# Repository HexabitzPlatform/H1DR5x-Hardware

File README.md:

# H1DR5x-Hardware
Hexabitz 10Base-T Ethernet Module Hardware Design

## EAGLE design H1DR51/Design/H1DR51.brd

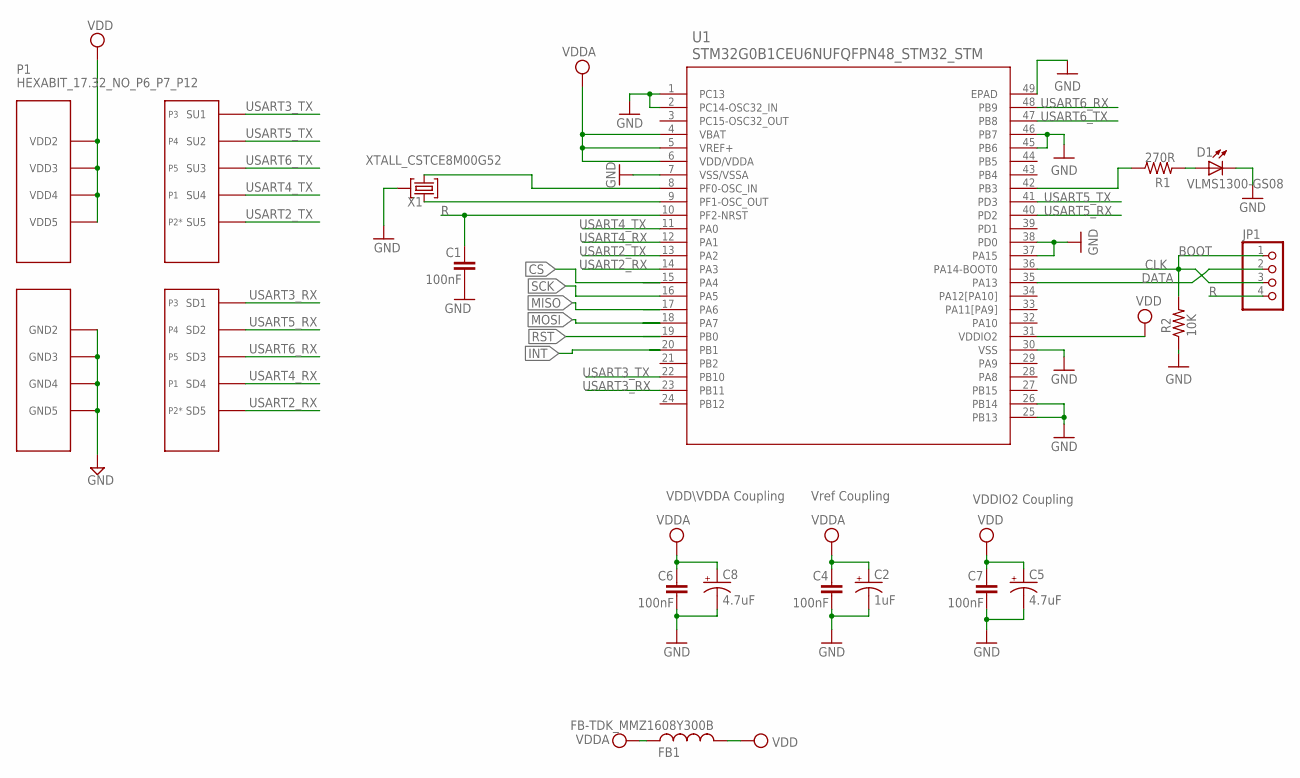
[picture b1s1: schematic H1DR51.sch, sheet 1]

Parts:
C1, C4, C6, C7: 100nF; C-0603
C2: 1uF; C-0805-POL
C5, C8: 4.7uF; C-0805-POL
D1: VLMS1300-GS08; MPN VLMS1300-GS08
FB1: FB-TDK_MMZ1608Y300B; MPN MMZ1608Y300B
JP1: PINHD-1X4; 1X04
P1: HEXABIT_17.32_NO_P6_P7_P12
R1: 270R; R-0603
R2: 10K; R-0603
U1: STM32G0B1CEU6NUFQFPN48_STM32_STM; UFQFPN48_STM32_STM
X1: XTALL_CSTCE8M00G52

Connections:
CLK: JP1.1, JP1.3, R2.2, U1.36 (PA14-BOOT0)
CS: U1.15 (PA4); also elsewhere on the board
DATA: JP1.2, U1.35 (PA13)
GND: C1.2, C2.2 (-), C4.2, C5.2 (-), C6.2, C7.2, C8.2 (-), D1.C, P1.PAD_PD8 (GND2), P1.PAD_PD9 (GND3), P1.PAD_PD10 (GND4), P1.PAD_PD11 (GND5), R2.1, U1.1 (PC13), U1.2 (PC14-OSC32_IN), U1.7 (VSS/VSSA), U1.25 (PB13), U1.26 (PB14), U1.30 (VSS), U1.37 (PA15), U1.38 (PD0), U1.45 (PB6), U1.46 (PB7), U1.49 (EPAD), X1.P$2 (2); also elsewhere on the board
INT: U1.20 (PB1); also elsewhere on the board
MISO: U1.17 (PA6); also elsewhere on the board
MOSI: U1.18 (PA7); also elsewhere on the board
unnamed: R1.1, U1.42 (PB3)
unnamed: D1.A, R1.2
unnamed: U1.9 (PF1-OSC_OUT), X1.P$1 (1)
unnamed: U1.8 (PF0-OSC_IN), X1.P$3 (3)
R: C1.1, JP1.4, U1.10 (PF2-NRST)
RST: U1.19 (PB0); also elsewhere on the board
SCK: U1.16 (PA5); also elsewhere on the board
USART2_RX: P1.PAD_PD5 (SD5), U1.14 (PA3)
USART2_TX: P1.PAD_PU5 (SU5), U1.13 (PA2)
USART3_RX: P1.PAD_PD1 (SD1), U1.23 (PB11)
USART3_TX: P1.PAD_PU1 (SU1), U1.22 (PB10)
USART4_RX: P1.PAD_PD4 (SD4), U1.12 (PA1)
USART4_TX: P1.PAD_PU4 (SU4), U1.11 (PA0)
USART5_RX: P1.PAD_PD2 (SD2), U1.40 (PD2)
USART5_TX: P1.PAD_PU2 (SU2), U1.41 (PD3)
USART6_RX: P1.PAD_PD3 (SD3), U1.48 (PB9)
USART6_TX: P1.PAD_PU3 (SU3), U1.47 (PB8)
VDD: C5.1 (+), C7.1, FB1.2, P1.PAD_PU8 (VDD2), P1.PAD_PU9 (VDD3), P1.PAD_PU10 (VDD4), P1.PAD_PU11 (VDD5), U1.31 (VDDIO2); also elsewhere on the board
VDDA: C2.1 (+), C4.1, C6.1, C8.1 (+), FB1.1, U1.4 (VBAT), U1.5 (VREF+), U1.6 (VDD/VDDA)

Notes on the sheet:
Vref Coupling
VDDIO2 Coupling
VDD\VDDA Coupling
BOOT
P2*

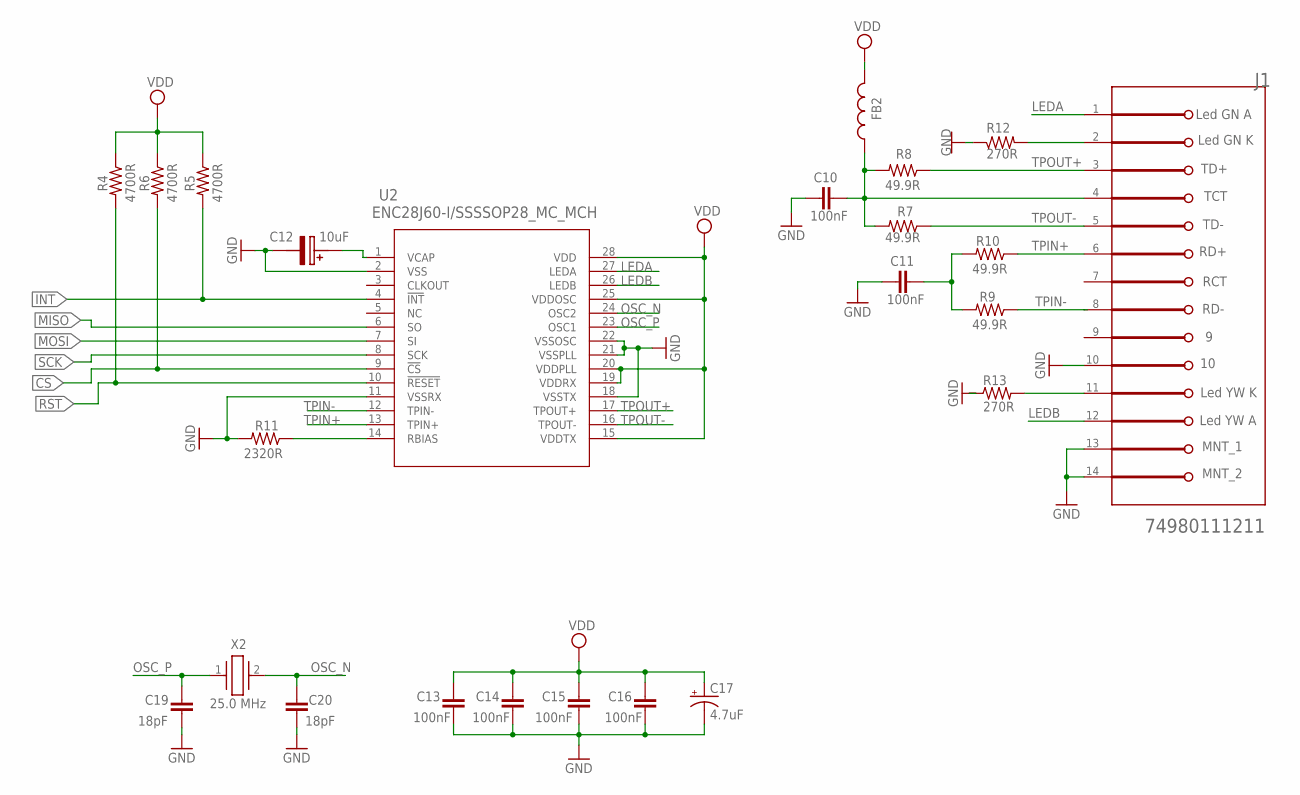
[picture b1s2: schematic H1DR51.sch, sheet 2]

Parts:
C10, C11, C13, C14, C15, C16: 100nF; C-0603
C12: 10uF; T491A
C17: 4.7uF; C-0805-POL
C19, C20: 18pF; C-0603
FB2: FB-TDK_MMZ1608Y300B; MPN MMZ1608Y300B
J1: WURTH_74980111211WURTH_74980111211_0_0; WURTH_74980111211_0
R4, R5, R6: 4700R; R-0603
R7, R8, R9, R10: 49.9R; R-0603
R11: 2320R; R-0603
R12, R13: 270R; R-0603
U2: ENC28J60-I/SSSSOP28_MC_MCH; SSOP28_MC_MCH
X2: 25.0 MHz; ABM325000MHZB2T

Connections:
CS: R6.2, U2.9 (!CS); also elsewhere on the board
GND: C10.2, C11.2, C12.2 (-), C13.2, C14.2, C15.2, C16.2, C17.2 (-), C19.2, C20.2, J1.10, J1.13 (MNT_1), J1.14 (MNT_2), R11.2, R12.1, R13.1, U2.2 (VSS), U2.11 (VSSRX), U2.18 (VSSTX), U2.21 (VSSPLL), U2.22 (VSSOSC); also elsewhere on the board
INT: R5.2, U2.4 (!INT); also elsewhere on the board
LEDA: J1.1 (GREEN_ANODE), U2.27 (LEDA)
LEDB: J1.12 (YELLOW_ANODE), U2.26 (LEDB)
MISO: U2.6 (SO); also elsewhere on the board
MOSI: U2.7 (SI); also elsewhere on the board
unnamed: C11.1, R9.2, R10.2
unnamed: C10.1, FB2.1, J1.4 (TCT), R7.2, R8.2
unnamed: R11.1, U2.14 (RBIAS)
unnamed: C12.1 (+), U2.1 (VCAP)
unnamed: J1.2 (GREEN_CATHODE), R12.2
unnamed: J1.11 (YELLOW_CATHODE), R13.2
OSC_N: C20.1, U2.24 (OSC2), X2.2
OSC_P: C19.1, U2.23 (OSC1), X2.1
RST: R4.2, U2.10 (!RESET); also elsewhere on the board
SCK: U2.8 (SCK); also elsewhere on the board
TPIN+: J1.6 (RD+), R10.1, U2.13 (TPIN+)
TPIN-: J1.8 (RD-), R9.1, U2.12 (TPIN-)
TPOUT+: J1.3 (TD+), R8.1, U2.17 (TPOUT+)
TPOUT-: J1.5 (TD-), R7.1, U2.16 (TPOUT-)
VDD: C13.1, C14.1, C15.1, C16.1, C17.1 (+), FB2.2, R4.1, R5.1, R6.1, U2.15 (VDDTX), U2.19 (VDDRX), U2.20 (VDDPLL), U2.25 (VDDOSC), U2.28 (VDD); also elsewhere on the board

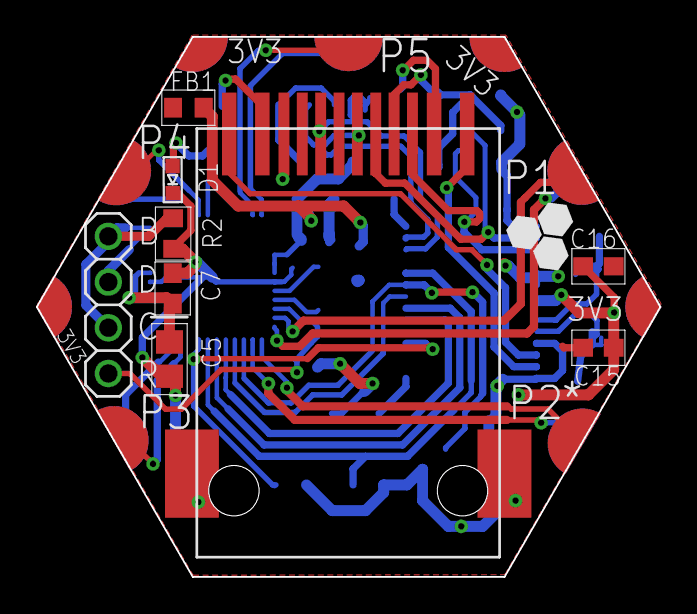
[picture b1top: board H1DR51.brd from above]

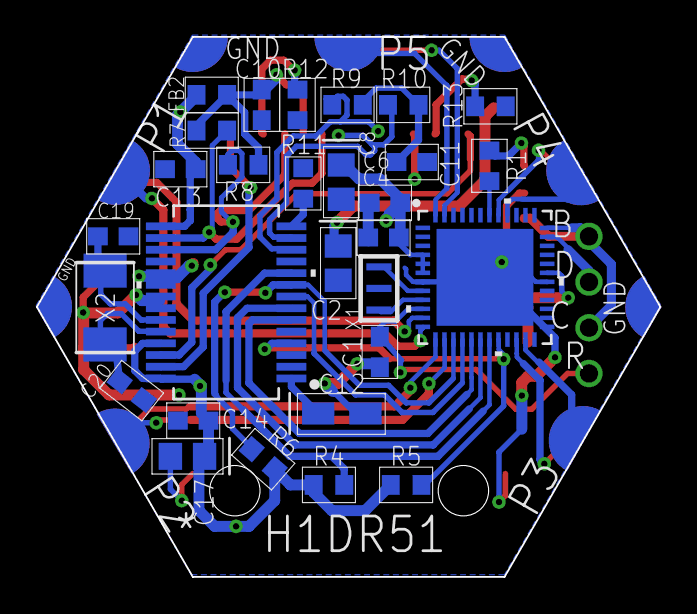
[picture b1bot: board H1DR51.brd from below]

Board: 2 copper layers, 34.6 x 30.0 mm, 39 parts (29 on the bottom side), 40 nets.

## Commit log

2022-08-23 Changing MCU to STM32G0
2023-02-15 -Correcting some documentaion issues
2023-03-05 -Correct some documentaion issues

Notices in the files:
parts and their libraries:
COPYRIGHT: Copyright (C) 2022 Ultra Librarian. All rights reserved.
